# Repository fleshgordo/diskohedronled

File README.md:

Diskohedronled
==============

Diskohedron (led version) 2014

A triacontahedron with 30 laser-etched rhombic faces, each containing a 4W RGBW(+White) LED. The first prototype consists of 30 3d-printed rhombic boxes which form a Triacontahedron. 

  * 30 x 4W RGBW
  * WIFI interface (android/iphone controllable, served by nodejs on beaglebone black)
  * Modular
  
Thanks to Bread'n'Butter in Lausanne and HEAD Option interaction in Geneva for making us use their Makerbot printers.

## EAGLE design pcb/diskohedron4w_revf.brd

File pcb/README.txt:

diskohedron.lbr -> put into your eagle library folder

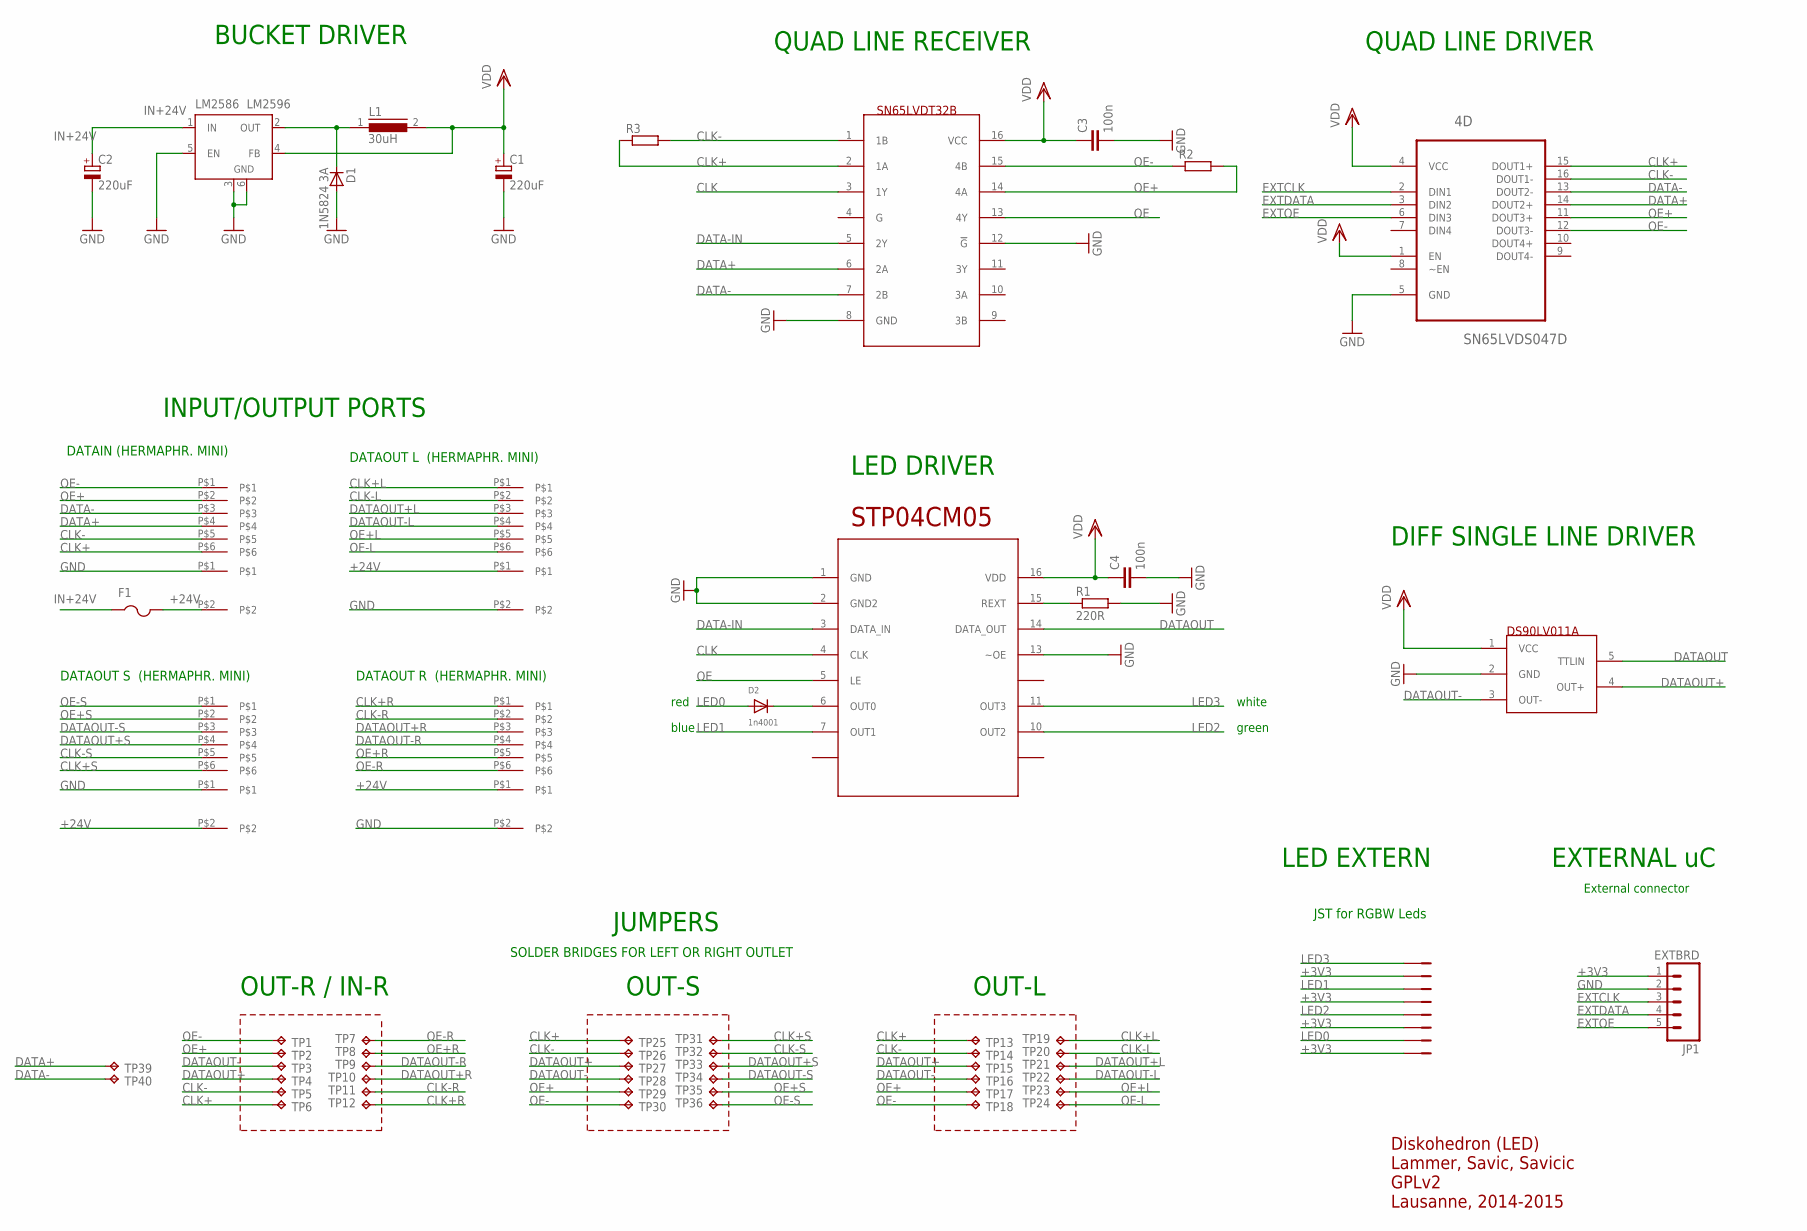
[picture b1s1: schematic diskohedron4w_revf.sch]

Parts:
1D: DS90LV011A; SOT23-5
4D: SN65LVDS047D; SOIC127P600X175-16N
4R: SN65LVDST32; SOIC16
C1, C2: 220uF; 153CLV-1010
C3, C4: 100n; C0805
D1: 1N5824 3A; DIODE_SMC
D2: 1n4001; SMADIODE
F1: PTCFUSE-1812; 1812
IN1: HERMAPHRODITMINI6PIN
JP1: EXTBRD; 1X05
JST: 8PIN-ZH; B8B-ZH
L1: 30uH; DR127
LM2586: LM2596; TO263-5
OUT-L: HERMAPHRODITMINI6PIN
OUT-R: HERMAPHRODITMINI6PIN
OUT-S: HERMAPHRODITMINI6PIN
POWERIN: HERMAPHRODIT2PIN
POWEROUT-L: HERMAPHRODIT2PIN
POWEROUT-R: HERMAPHRODIT2PIN
POWEROUT-S: HERMAPHRODIT2PIN
R1: 220R; M0805
R2, R3: R-EU_R0603; R0603
STP04: STP04CM05; TSSOP16
TP1, TP2, TP5, TP6, TP7, TP8, TP11, TP12, TP13, TP14, TP15, TP16, TP17, TP18, TP19, TP20, TP21, TP22, TP23, TP24, TP25, TP26, TP27, TP28, TP29, TP30, TP31, TP32, TP33, TP34, TP35, TP36: TPTP12SQ; TP12SQ
TP3, TP4, TP39, TP40: TPTP09SQ; TP09SQ
TP9, TP10: TPTP20SQ; TP20SQ

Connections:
+3V3: 1D.1 (VCC), 4D.1 (EN), 4D.4 (VCC), 4R.16 (VCC), C1.+, C3.1, C4.1, JP1.1, JST.2, JST.4, JST.6, JST.8, L1.2, LM2586.4 (FB), STP04.16 (VDD)
+24V: F1.2, POWERIN.P$2, POWEROUT-L.P$1, POWEROUT-R.P$1, POWEROUT-S.P$2
CLK: 4R.3 (1Y), STP04.4 (CLK)
CLK+: 4D.15 (DOUT1+), 4R.2 (1A), IN1.P$6, R3.1, TP6.TP, TP13.TP, TP25.TP
CLK+L: OUT-L.P$1, TP19.TP
CLK+R: OUT-R.P$1, TP12.TP
CLK+S: OUT-S.P$6, TP31.TP
CLK-: 4D.16 (DOUT1-), 4R.1 (1B), IN1.P$5, R3.2, TP5.TP, TP14.TP, TP26.TP
CLK-L: OUT-L.P$2, TP20.TP
CLK-R: OUT-R.P$2, TP11.TP
CLK-S: OUT-S.P$5, TP32.TP
DATA+: 4D.14 (DOUT2+), 4R.6 (2A), IN1.P$4, TP39.TP
DATA-: 4D.13 (DOUT2-), 4R.7 (2B), IN1.P$3, TP40.TP
DATA-IN: 4R.5 (2Y), STP04.3 (DATA_IN)
DATAOUT: 1D.5 (TTLIN), STP04.14 (DATA_OUT)
DATAOUT+: 1D.4 (OUT+), TP4.TP, TP15.TP, TP27.TP
DATAOUT+L: OUT-L.P$3, TP21.TP
DATAOUT+R: OUT-R.P$3, TP10.TP
DATAOUT+S: OUT-S.P$4, TP33.TP
DATAOUT-: 1D.3 (OUT-), TP3.TP, TP16.TP, TP28.TP
DATAOUT-L: OUT-L.P$4, TP22.TP
DATAOUT-R: OUT-R.P$4, TP9.TP
DATAOUT-S: OUT-S.P$3, TP34.TP
EXTCLK: 4D.2 (DIN1), JP1.3
EXTDATA: 4D.3 (DIN2), JP1.4
EXTOE: 4D.6 (DIN3), JP1.5
GND: 1D.2 (GND), 4D.5 (GND), 4R.8 (GND), 4R.12 (!G), C1.-, C2.-, C3.2, C4.2, D1.A (C), JP1.2, LM2586.3 (GND), LM2586.5 (EN), LM2586.6 (GND), POWERIN.P$1, POWEROUT-L.P$2, POWEROUT-R.P$2, POWEROUT-S.P$1, R1.2, STP04.1 (GND), STP04.2 (GND2), STP04.13 (~OE)
IN+24V: C2.+, F1.1, LM2586.1 (IN)
LED0: D2.A, JST.7
LED1: JST.3, STP04.7 (OUT1)
LED2: JST.5, STP04.10 (OUT2)
LED3: JST.1, STP04.11 (OUT3)
unnamed: R1.1, STP04.15 (REXT)
unnamed: D1.C (A), L1.1, LM2586.2 (OUT)
unnamed: D2.C, STP04.6 (OUT0)
OE: 4R.13 (4Y), STP04.5 (LE)
OE+: 4D.11 (DOUT3+), 4R.14 (4A), IN1.P$2, R2.2, TP2.TP, TP17.TP, TP29.TP
OE+L: OUT-L.P$5, TP23.TP
OE+R: OUT-R.P$5, TP8.TP
OE+S: OUT-S.P$2, TP35.TP
OE-: 4D.12 (DOUT3-), 4R.15 (4B), IN1.P$1, R2.1, TP1.TP, TP18.TP, TP30.TP
OE-L: OUT-L.P$6, TP24.TP
OE-R: OUT-R.P$6, TP7.TP
OE-S: OUT-S.P$1, TP36.TP

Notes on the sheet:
QUAD LINE RECEIVER
LED DRIVER
DIFF SINGLE LINE DRIVER
BUCKET DRIVER
DATAOUT L (HERMAPHR. MINI)
DATAOUT R (HERMAPHR. MINI)
DATAIN (HERMAPHR. MINI)
External connector
JST for RGBW Leds
SOLDER BRIDGES FOR LEFT OR RIGHT OUTLET
JUMPERS
Diskohedron (LED) Lammer, Savic, Savicic GPLv2 Lausanne, 2014-2015
QUAD LINE DRIVER
INPUT/OUTPUT PORTS
EXTERNAL uC
red
blue
green
white
DATAOUT S (HERMAPHR. MINI)
OUT-R / IN-R
OUT-S
OUT-L
LED EXTERN

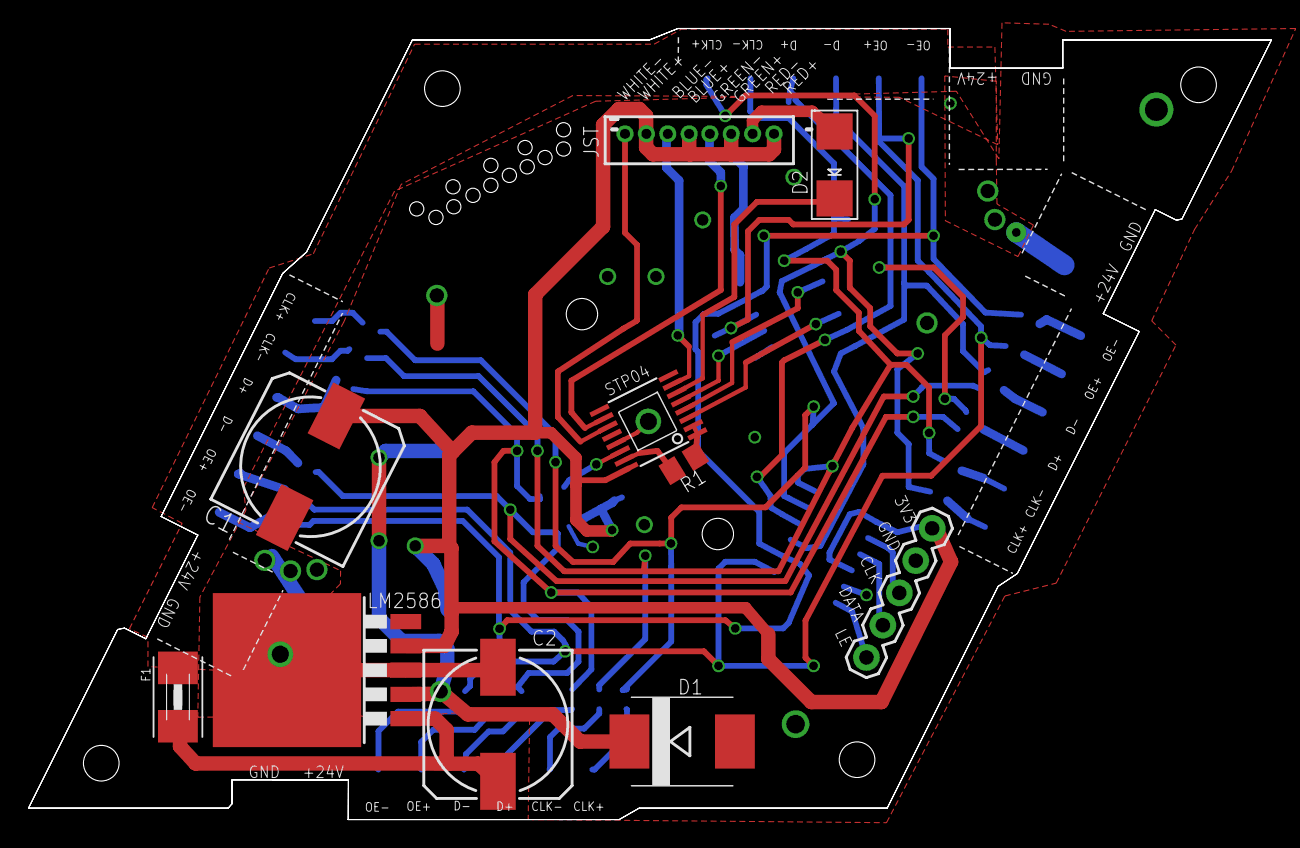
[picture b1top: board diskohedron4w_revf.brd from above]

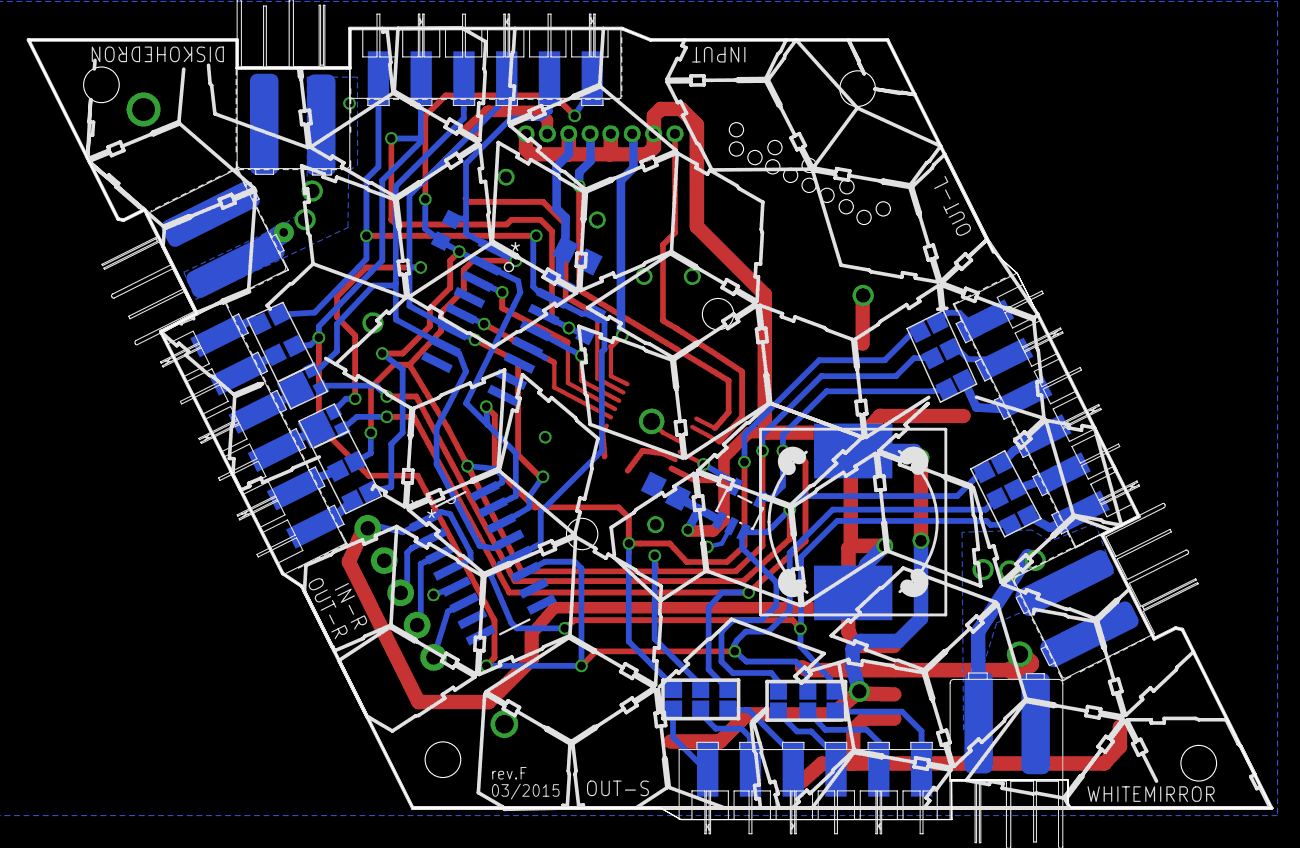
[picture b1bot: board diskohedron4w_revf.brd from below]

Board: 2 copper layers, 87.2 x 55.5 mm, 64 parts (54 on the bottom side), 44 nets.

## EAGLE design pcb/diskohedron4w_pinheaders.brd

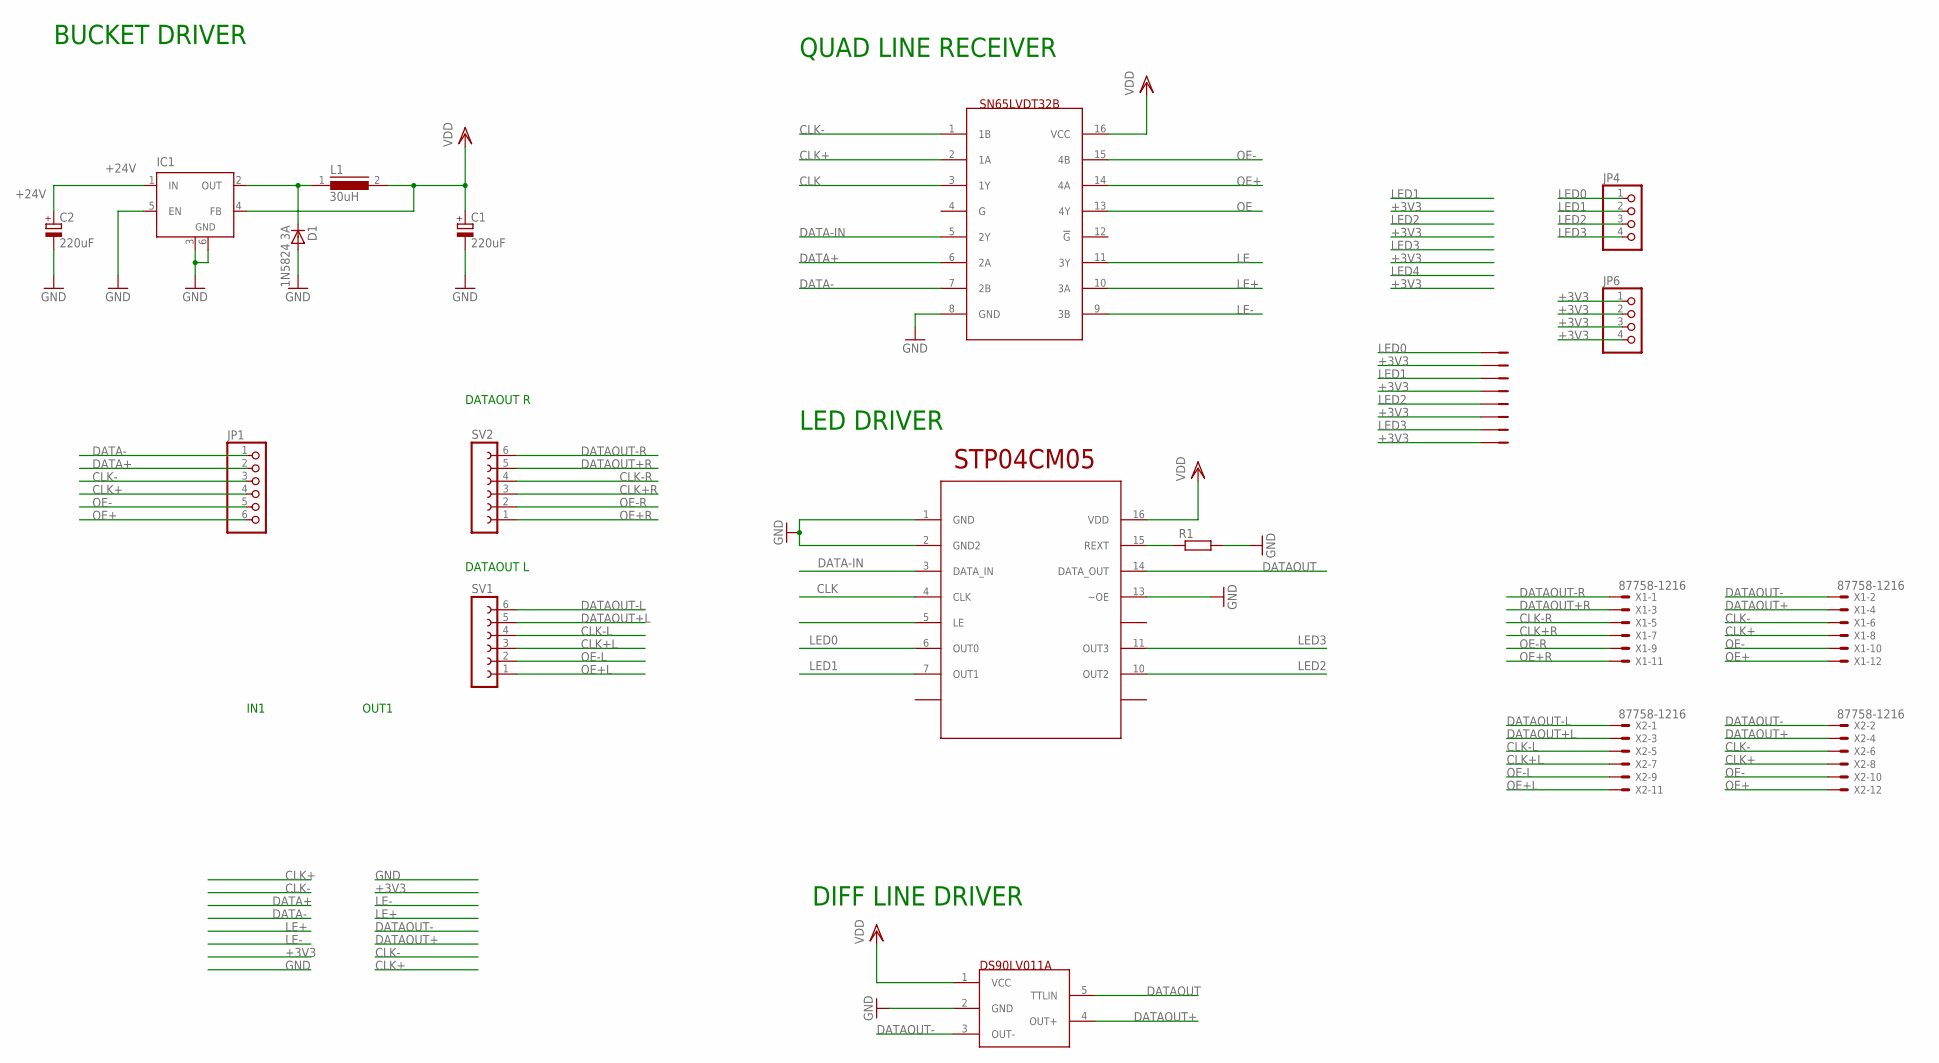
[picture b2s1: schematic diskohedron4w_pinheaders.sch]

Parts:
C1, C2: 220uF; 153CLV-1010
D1: 1N5824 3A; DIODE_SMC
IC1: LM2596S; TO263-5
JP1: PINHD-1X06_2.54-90°; 1X06/90
JP4, JP6: PINHD-1X4; 1X04
L1: 30uH; DR127
R1: R-EU_M0805; M0805
SV1, SV2: FE06W
U$1: STP04CM05; TSSOP16
U$2: SN65LVDST32; SOIC16
U$3: DS90LV011A; SOT23-5
U$4: 8PIN-ZH; B8B-ZH
X1, X2: 87758-1216

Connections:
+3V3: C1.+, IC1.4 (FB), JP6.1, JP6.2, JP6.3, JP6.4, L1.2, U$1.16 (VDD), U$2.16 (VCC), U$3.1 (VCC), U$4.2, U$4.4, U$4.6, U$4.8
+24V: C2.+, IC1.1 (IN)
CLK: U$1.4 (CLK), U$2.3 (1Y)
CLK+: JP1.4, U$2.2 (1A), X1.8, X2.8
CLK+L: SV1.3, X2.7
CLK+R: SV2.3, X1.7
CLK-: JP1.3, U$2.1 (1B), X1.6, X2.6
CLK-L: SV1.4, X2.5
CLK-R: SV2.4, X1.5
DATA+: JP1.2, U$2.6 (2A)
DATA-: JP1.1, U$2.7 (2B)
DATA-IN: U$1.3 (DATA_IN), U$2.5 (2Y)
DATAOUT: U$1.14 (DATA_OUT), U$3.5 (TTLIN)
DATAOUT+: U$3.4 (OUT+), X1.4, X2.4
DATAOUT+L: SV1.5, X2.3
DATAOUT+R: SV2.5, X1.3
DATAOUT-: U$3.3 (OUT-), X1.2, X2.2
DATAOUT-L: SV1.6, X2.1
DATAOUT-R: SV2.6, X1.1
GND: C1.-, C2.-, D1.A (C), IC1.3 (GND), IC1.5 (EN), IC1.6 (GND), R1.2, U$1.1 (GND), U$1.2 (GND2), U$1.13 (~OE), U$2.8 (GND), U$3.2 (GND)
LE: U$1.5 (LE), U$2.11 (3Y)
LE+: U$2.10 (3A)
LE-: U$2.9 (3B)
LED0: JP4.1, U$1.6 (OUT0), U$4.1
LED1: JP4.2, U$1.7 (OUT1), U$4.3
LED2: JP4.3, U$1.10 (OUT2), U$4.5
LED3: JP4.4, U$1.11 (OUT3), U$4.7
unnamed: R1.1, U$1.15 (REXT)
unnamed: D1.C (A), IC1.2 (OUT), L1.1
OE: U$2.13 (4Y)
OE+: JP1.6, U$2.14 (4A), X1.12, X2.12
OE+L: SV1.1, X2.11
OE+R: SV2.1, X1.11
OE-: JP1.5, U$2.15 (4B), X1.10, X2.10
OE-L: SV1.2, X2.9
OE-R: SV2.2, X1.9

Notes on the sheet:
QUAD LINE RECEIVER
LED DRIVER
DIFF LINE DRIVER
IN1
OUT1
BUCKET DRIVER
DATAOUT L
DATAOUT R

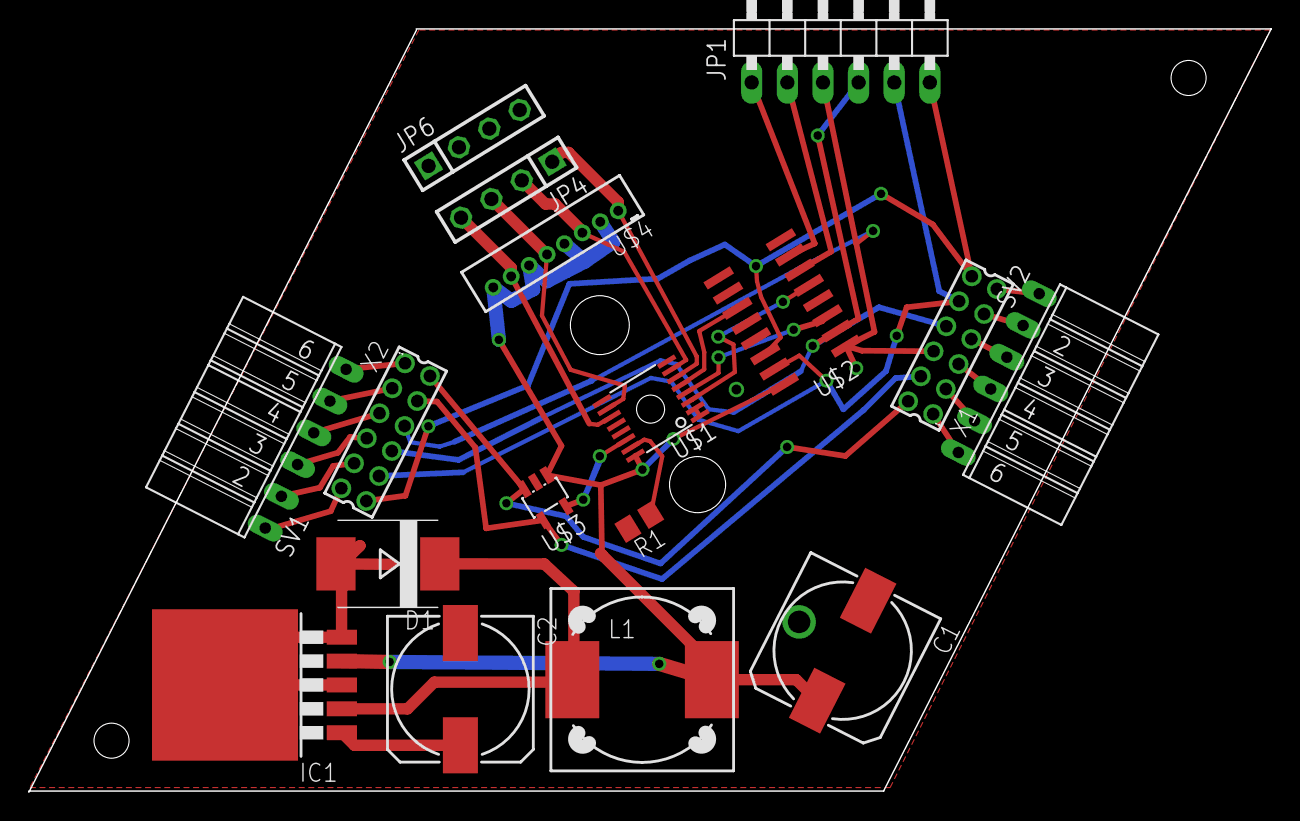
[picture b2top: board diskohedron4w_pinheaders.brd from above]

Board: 2 copper layers, 88.6 x 54.4 mm, 17 parts (0 on the bottom side), 33 nets.

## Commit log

2014-05-03 git init + 3d model
2014-05-03 added pcb
2014-05-03 updated pcb
2014-05-04 first pcb freeze
2014-05-06 rev. a almost fixed, first gerber-cam process
2014-05-06 updated gerbers
2014-05-09 last commit before changing physical dimension
2014-05-11 order for itead 12/05/2014 #100029337
2014-05-24 remodelled the bottom with a big hole and corners for attaching pcb rev. a
2014-05-29 first commit for rev.b after wrong hermaphrodite spotting
2014-05-31 changed output bridges to SMD pads, some cleanup, some labelling for bsilk
2014-05-31 cleanup rev.b swapped single line driver to bottom side
2014-06-01 digital line driver and receiver swapped to bottom, major redesign
2014-06-01 further cleaning, added bottomlayer cream masks for smd bridges
2014-06-06 order itead for rev.b and 3d trio unique model
2014-06-07 cleaning pcb dir
2014-06-07 added powersupply dwg
2014-06-08 power unit cone before murging objects
2014-06-16 first draft of rev. c with switchable input/output
2014-06-19 freezing gerber for rev.c, powercone 3d part
2014-06-20 cleaned up schematic of rev.c
2014-06-24 finished power unit UFO + L
2014-07-08 cleanup revision b
2014-07-10 edited stencil layout
2014-07-10 stencil, acrylglass
2014-07-17 initial commit phil (changed ShiftPWM library + diskoLEDron arduino sketch)
2014-08-02 documentation for mounting
2014-09-01 added setRGBW(ledNumber, r, b, g, w)
2014-09-03 stencil files and partlist updated
2014-09-08 last modifications on the boxes made in july in vienna
2014-12-09 added lasercutting folder with a powerunitcone face (.dxf)
2014-12-09 lasercutting powerunitcone dwg file
2014-12-14 finally, the lasercutting file from the versalaser machine
2014-12-30 rev.d and beagle upload scripts
2014-12-30 moved upload.sh
2014-12-30 upload.sh - filename can be in subfolder
2014-12-30 added shutdown script beaglebone
2015-02-18 added upload.sh script for remote upload of arduino hex files
2015-02-22 new testprog for temperature sensor DHT22
2015-02-25 added termination resistors for rev.c & d
2015-03-02 added stencil for rev.d
2015-03-05 added rev.E; changed CAPS To CASE G
2015-03-26 changed to revF for itead order & modifed BOM list
2015-03-28 added top mounting screenshot
2015-03-28 dxf push push push
2015-03-28 ordered stl files for revB
2015-03-28 revF ready for print; changed holes; created with Rhino
2015-03-30 order in 3model stl folder
2015-04-02 added assembly instruction for itead
2015-04-09 upload script for black lamp
2015-04-11 added master/salve python code for expo bienne
2015-04-12 after biel
2015-04-12 added assembly screenshot and small change in board silkscreen layout
2015-04-14 added programs for biel (black + white), added DHT temperature sensor library
2015-04-15 cleaned up .DS_STORE
2015-04-16 mapping lightbulbs for zwarte de zwart, phil's hand > inkscape
2015-05-11 3D stuff
2016-01-05 documenting construction - order of cells / bulbs
2016-01-06 software cleanup + basel software
2016-01-06 first commit for app/www
2016-01-06 further cleaning and making this comment for phil :)
2016-01-07 loading and saving presets, diskoserver.js writing presetfile
2016-01-07 added publish www script for easier deployment
2016-01-07 fixing preset and added rgbw mode
2016-01-10 adding doc for software and medium-done new presets for sinusRGBW....)
2016-01-11 3d construction files updates
2016-01-11 3d files updates, standoffs
2025-01-06 fixing serialport js for new version
2025-01-09 New ShiftPWM Library with SetRGBWSimple function
2025-01-10 updated serialporrt
2025-01-10 fixing firmware

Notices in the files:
parts and their libraries:
SparkFun-Connectors: Licensing: Creative Commons ShareAlike 4.0 International - https://creativecommons.org/licenses/by-sa/4.0
